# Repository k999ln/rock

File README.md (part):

# avokado / mii

miiは、声でEveに頼み、部屋に映った成果を手で操作するために開発している空間コンピューターです。

空間SIの現行研究: [mii・部屋全体を裸眼／工事なしで表示する新規開発設計](docs/mii/design/28-room-scale-si-rd.md)。共通OSを維持し、出射面の反例計算、研究部品、段階予算を整理。卓上は製品目標にせず、全室の物理成立は未実証。

**[NoahでAgentを試す](https://avoado.si/noah)**　·　[18秒で操作を見る](#catalog)

公開サイト `avoado.si` はNoahのストア・検索・実行・保存・Agent制作を入口に、必要なEve・接続・設定へ進む構成です。別企画・課金テストの画面は公開終了し、旧URLは対応する現行画面へ転送します。審査画面は審査担当だけが開けます。対象は[task139](codex/tasks/139-main-public-pages.md)、公開URLの正本は[ページ定義](services/sky-web/main-page-policy.mjs)です。

<a href="https://avocadomini.si/#technology">
  <picture>
    <source media="(prefers-reduced-motion: reduce)" srcset="docs/assets/readme/mii-tower-on-dock.webp">
    
  </picture>
</a>

*miiの外観と内部構造を描いたコンセプト映像。* [公式サイトで構造を見る](https://avocadomini.si/#technology)

[暮らしの短編](#films) · [miiの構造](#mii) · [Eveに頼む](#eve) · [Noahで探す](#catalog) · [Macで試す](#noah-mac) · [全体構成](#architecture) · [開発状況](#status) · [コードと検証](#development)

## 暮らしの中のmii

料理で両手がふさがっているとき、手を止めずに残り時間を確かめる。公式サイトの短編「料理」は、その使い心地を描いています。

*公式サイトの5本の短編。朝の光、集中するときの日よけ、外での制作、料理中のタイマー、夜の足元の灯りを描いたコンセプト映像です。*

[朝](https://d8j0ntlcm91z4.cloudfront.net/user_3ImsN7zDg5XAxCTCNf16qVkxzVQ/hf_20261028_201649_fe60d9fe-0cb2-4101-b833-4afbc7cfe769.mp4)　·　[集中](https://d8j0ntlcm91z4.cloudfront.net/user_3ImsN7zDg5XAxCTCNf16qVkxzVQ/hf_20261028_201649_1efcbbf2-15f6-4650-8089-16a7679b7ce3.mp4)　·　[創作](https://d8j0ntlcm91z4.cloudfront.net/user_3ImsN7zDg5XAxCTCNf16qVkxzVQ/hf_20261028_202029_48890df7-1fdf-49bf-b749-eae800aacdd5.mp4)　·　[料理](https://d8j0ntlcm91z4.cloudfront.net/user_3ImsN7zDg5XAxCTCNf16qVkxzVQ/hf_20261028_201647_7fafb347-3f1d-47e2-97fd-67e407a11d1c.mp4)　·　[夜](https://d8j0ntlcm91z4.cloudfront.net/user_3ImsN7zDg5XAxCTCNf16qVkxzVQ/hf_20261028_201650_242a20a0-0837-4b0a-827b-c90c76088834.mp4)

## 声と手を受け取る、4本のTowerとHub

部屋の中で表示を指すと、四方向のTowerが手の位置を捉えます。別体のHub上でRockstarOSが入力をまとめ、表示層に渡す設計です。表示層は使う空間に合わせて差し替えられます。Towerが1本のときは、Eveの機能を限定して使う想定です。

*Tower上部のセンサー帯のデザイン案。* [miiの構造](docs/structure/01-mii.md) · [R5設計](docs/avocado-mini-r5/README.md) · [V2の比較研究](docs/mii/design/v2-study/README.md)

<details>
<summary>空間入力とMaterial Inventionの実装を見る</summary>

空間入力の実装と機種設定から、手の入力がどこで処理されるかを追えます。Material Inventionには再計算用sandboxと設計資料があり、シミュレーション・実験室接続は未実装です。[空間入力のコード](lib/mii-spatial-input.ts) · [機種設定](systems/rock-star-os/targets/avocado-mini/) · [Material Inventionの設計](docs/rockstaros-avocado-mini-complete-design.md) · [製品サイトのコード](sites/avocado-mini/)

</details>

## Eveに、やりたいことを伝える

「今週の学習メモを、次に調べたいことと一緒に整理したい」。Eveでは、まず依頼を自分の言葉で書きます。入力欄の下で実行先・担当・基盤モデルを確認し、その仕事をどこに任せるか選びます。

*Web版の実画面。依頼を書いたところで、実行先はまだ接続していません。* 会話は履歴から、依頼した仕事と成果は「仕事と成果」から開けます。実行には本人確認とToolへの接続・権限が必要です。[Eveを開く](https://avoado.si/os/eve)

<details>
<summary>Eveが依頼を工程に分け、成果を検収する仕組み</summary>

### 仕事の工程と検収

Eveが目的を聞き、必要な道具とAgentを組み合わせます。AMCが工程・担当・合格条件を決め、Jevが結果を独立して検収します。下のデモでAMCの実行、別プロセスでの検収、差し戻しと再計画を試せます。成果の編集・持ち出しは、その仕事の保存方式に従います。

```sh
npm run amc:cycle -- demo
```

工程の組み合わせ、見積り、会社受注の分配を計算するライブラリと、募集文面を判定するCLIがあります。外部への応募・契約・納品・送金までの接続は開発中です。[仕事の計画](docs/sky-work-loop.md) · [実行・停止・復旧](docs/amc-goal-orchestrator.md#goalから逆算するローカル実行と再計画)

</details>

<details>
<summary>Eveのコードと担当設定</summary>

| コード | 内容 |
| --- | --- |
| [app/os/eve/](app/os/eve/) / [components/sky-chat-workspace.tsx](components/sky-chat-workspace.tsx) | 会話・仕事・Toolの画面 |
| [lib/workflow.ts](lib/workflow.ts) / [lib/work-store.ts](lib/work-store.ts) | 状態遷移・本人別保存・revision競合判定 |
| [docs/structure/04-eve-noa-amc-sky.md](docs/structure/04-eve-noa-amc-sky.md) | Eveと担当構成・実行・評価の責任 |
| mii本体の組立設計（OS共通・4 Tower＋専用Hub） | [本体HW1: 型番・端子・配線](docs/mii/design/19-body-hardware.md) / [共通OS](docs/mii/design/14-common-os.md) / [開発用検証装置](docs/mii/design/18-parts-wiring.md) |

担当設定は[全社役割台帳](data/company-role-map.json)、[営業担当台帳](data/revenue-role-map.json)、[担当別の設定](.cursor/agents/)にあります。

</details>

## Noahで、仕事に合うAgentを探す

eSIM案内と「登録情報」では、保存した氏名・メールなどを次のAgent登録にも使う目的と、送信先・項目の確認、再利用の停止を説明します。共通プロフィールは暗号化して保存します。Apple／Googleからの自動取込みと事業者への実申込は準備中です。[登録情報の再利用設計](docs/structure/03-esim.md#登録情報を次のagentでも使う2026-11-26)

本人用の[収益業務パック](docs/services/noah-revenue-pack.md)は、携帯とPCで共通のNoah画面から商品設計・納品サンプル・提案書の3担当を実行します。本人用クラウドに成果を保存し、Macの起動は不要です。無料枠を超えると待機・停止します。出力は確認用の下書きで、販売・応募・入金の完了を表しません。

*11月26日にスマホ幅390pxで開いた公開ホーム。* [旧Todayの画面](docs/assets/readme/noah-store-today.webp)

[登録フォームで生成した「法人のsi導入準備」の表紙を見る（4秒）](docs/assets/readme/noah-agent-motion.mp4)

[Noahのストア](https://avoado.si/noah)を開くと、「Agentを見つける」に接続できるAgentが並びます。上部で検索し、カテゴリや「すべて」「新しく見つかった」で絞り込めます。下へスクロールすると続きが表示されます。検索結果、保存したボード、自分のAgent、マーケットでもAgentごとの作品や仕事内容を表すカードから選べます。

作者は右上メニューの[Agentエンジニアリング](https://avoado.si/noah/engineering)でEveに目的を相談できます。実行先を確認して送ると、EveがNoahの無料クラウドで「どのAgentが何を受け取り、次に何を渡すか」を提案します。目的型なら本人の目的、収益型なら案件の成果地点と確認方法を示します。提案を読んでから試運転を選べます。紹介案件の組み合わせ例では、申込承認時と入金後の作者の取り分を見比べられます。同じ画面から自作・外部接続・動作確認・掲載申請へ進めます。

Agent登録と掲載申請では、自分の画像・動画を表紙に指定できます。迷ったときは「おまかせ生成」で、名前と説明から4秒の動画を作り、プレビューを見て選べます。CallMCPの詳細では、予約確認の依頼例と通話メモ、KaiCallsの利用条件を読んでから接続できます。購入・作者の掲載管理はストアから開けます。「法人のsi導入準備」の詳細では、業務の整理票ができるまでを15秒の短編で見られます。

専用eSIMの案内画面では利用条件と準備状況を確認できます。外部Agentに依頼するときは、提供元と送信先を確認します。[保存した成果](https://avoado.si/noah/my?view=saved&tab=results)・[eSIMの導入](https://avoado.si/connect)

保存した成果を開くと、仕事ごとの利用明細で使用量と料金の確定状況を確認できます。専用クラウドの利用権がある場合に、同じ成果一覧から仕事ごとのCPU使用量・計算料・Agent料・予約額を表示する機能も実装しています。本番での実請求は受入前です。

**[Eve・Noah 図解設計書](docs/noah/illustrated-specifications.md)**　利用者の操作、画面とバックエンド、eSIM、作者収益・作業料・定期便までを8枚の図で読めます。[共有用PDF](docs/assets/noah-illustrated-specifications.pdf)

受付中の仕事は、一覧の該当するAgentカードから開けます。「お店・会社のサイト運営」では保守・制作会社との打ち合わせに使う診断結果と確認事項を、「自分のメモ整理」では誰が何を担当するか、あとから見返せるメモを受け取れます。その時に受付可能な仕事を選べます。選ぶ前に受け取れる成果が分かり、詳細で入力・送信先を確かめて本人が依頼します。完了後は「保存した成果を見る」から開き直せます。画面とバックエンドの接続、データの取得元、初めて使う人に試してもらう手順は[初回利用の構造図](docs/noah/first-use-architecture.md)にまとめています。

基盤の仕様は[専用eSIMの発行・端末への導入・利用時の回線照合](docs/structure/03-esim.md)、[Noahクラウドの受付・実行・成果保存](docs/services/noah-cloud-agents.md)、[自社設備を含むクラウドの配置と運用](docs/compute-placement.md)にあります。公開NoahはWi-Fiや今のSIMで使えます。専用eSIMを必要とするRockstarOSの入口は模擬回線まで検証しています。Eveで担当を作る作者、Noahで依頼する利用者、外部から実入金を照合する運営のつながりは[報酬と定期便の構造図・計算例](docs/noah/eve-distribution-and-rewards.md)で確認できます。

公開Gradio APIと公開MCPに対応するAgentは、詳細の「使う」から入力して実行でき、進捗と成果をNoahの同じ仕事画面に保存します。実行中は仕事詳細を開いたままにし、保存された成果は後から再表示できます。結果通信が途切れた場合は自動再実行しません。APIのないコード紹介や提供元のGPU制限は、準備・失敗理由を表示します。

掲載リポジトリやパッケージは「使う」で提供元の公開接続定義を確認します。GitHub・npm・Dockerの公式配布記録を照合し、接続できるものはNoah内で入力・実行・成果保存へ進みます。本人認証や未対応のCLIが必要な場合は理由を表示します。掲載・定義取得・実行成功は区別します。

掲載Agentをどこまで使えるかは[実行経路別の判定表](docs/services/noah-cloud-agents.md#掲載agentの実行判定)で確認できます。11月25日に再調査した「実行準備が必要」の2,428件では、手元で8件、提供元で2件の成果を受け取りました。この対象からNoah本番で新たに成果を受け取った件数は0件です。

CLIの管理クラウドは、Memory・Filesystem・Sequential ThinkingにTime・bossの面接準備・Hermesの計画/依頼内メモを加え、公式6種類の対応機能を追加契約なしの無料枠で公開しています。対応範囲は [task125](codex/tasks/125-noah-cloud-agents.md) に記録しています。Hermes・boss-agent-cli・Time・Sequential Thinking・Memory・Filesystemの公式固定版を依頼ごとの隔離環境で動かします。標準入出力MCPの4配布物は外部通信なしのLinuxで起動・実ツール応答を確認し、Memoryの依頼間分離、Filesystemの作成/読込/作業領域外の拒否、生成物のhashも確認しました。固定応答の検査に加え、実モデル `gpt-oss-20b` で6配布物の道具実行・成果生成の成功例を手元の隔離Linuxで確認しました。空本文による継続通信の失敗を修正し、道具を実行しない完了報告は受け付けません。モデルの形式エラーによる失敗例もあり、本番クラウドでの受入とは区別します。無料のWorkers実行器は公式JavaScript本体を組み込み、3種類とも本番Noahから実モデルと公式Toolで処理し、Chrome全終了後の成果保存・再表示・ファイルの内容/hash一致を確認しました。本番の上限はUTC日ごとに本人3件・全体10件、1件240秒です（2026年11月26日確認）。Memoryの作業中の記憶は依頼ごとに分離し、出力ファイルは成果として保存します。公式TimeのMCP・bossの面接準備コマンド・Hermes本体の計画/依頼内メモは、種類ごとの非公開Python Workerで動かします。3種とも本番Noahから実モデルと公式処理を実行し、スマホ幅390pxのChromeを全終了した後のD1保存、保存一覧からの再表示・再読込・ファイルの内容/hash一致を確認しました。128MB制限での失敗はWorker分離で対処し、bossの出力上限とHermesの道具未実行も上限を増やさず補正しました。文章だけの完了を成功にはしません。Hermesのshell/一般ファイル操作、bossの求人検索/応募はこの無料版では扱いません。提供元の公開server.json、npmと公式MCP台帳、Docker公式配布記録から接続先を照合し、利用者にコード取込を求めずNoahの入力とWork保存へ進む処理も追加しています。全掲載の対応状況は `scripts/noah-agent-coverage.mjs` で点検し、定義確認を実行成功とは数えません。

11月26日に実行用Workerの配備履歴を確認し、全トラフィックを受けている版を[配備記録と受付コード](https://github.com/iceiceice999/rock/pull/58)に照合しました。Gitの `main` には、モデル使用量をUTC日ごとに本人2,400・全体8,000 neuronまでとし、件数にも本人12件・全体60件の安全上限を設ける変更があります。この変更は実行用Workerへの配備待ちです。[無料枠と配備条件](codex/tasks/125-noah-cloud-agents.md#2026-11-24-無料のクラウドを使ったモデルの量で数える)

管理クラウドの依頼は画面を閉じても実行が続き、右上メニューの「実行中」「保存した成果を見る」から本文とファイルを開けます。成果の閲覧ではAgentを再実行しません。スマホ幅390pxのChromeで全終了後の保存と再表示、実行中の停止・再読込保持を確認しています。実機Pixelの新クラウド受入とは区別します。保存済みファイルには未保存の注記を出さず、添付データが届いていない従来の結果には注記を維持します。

Agent詳細の「共有」「URLをコピー」「Xで紹介」から、個別AgentへのURLを渡せます。公開掲載中のAgentの名前・説明を共有カードへ反映し、接続情報や本人の成果は共有しません。

`https://avoado.si/` と `https://avoado.si/noah` の共有情報は、Noahのタイトル・説明・1200×630 PNGを返します。X用の大型画像カードとOpen Graphを初期HTMLに含め、画像添付なしでURL共有に使えます。

カードには元サイトの実際の評価数だけを表示します。件数のないMCP Registry等は詳細の出典で確認でき、評価として表示しません。

ホームには接続できるAgentが先に並びます。設定済みの管理クラウドで使える公式CLIも、詳細画面と同じ対応判定でこの一覧と検索へ含めます。未設定・無料版で未対応のCLIは含めません。指定した条件を保持して検索し、共通カードの一つの結果一覧に表示します。法人向け導入準備・組合せガイドの告知枠はホームから外しています。

検索は [Agentを探す](https://avoado.si/noah)、保存は [保存したもの](https://avoado.si/noah/saved) にまとめています。保存はボード・Agent・担当・成果・ファイルを切り替えます。旧URLは対応するカテゴリへ移り、Noah配下のMac専用・投稿・コミュニティー・大学別ページは撤去済みです。本人Mac Runnerの接続承認URL `/noah/mac/connect` は、接続時に発行されるコードを確認するために保持します。保存データは保持しています。

Agent詳細の最初に料金・送信先と接続ボタンを表示します。接続後は用途名で操作を選び、その行の下から依頼できます。スマホの操作一覧も、用途名・説明・確認事項を縦に並べて読めます。長い紹介は「Agentの詳細」で開けます。任せる範囲・提供者の説明は開いて確認でき、必要入力と実行を選んだ行の近くに表示します。

説明の段では、必要な準備から接続と依頼までの順番を確認できます。素材の札は、根拠を確認して公開する段階で表示します。

一覧の読み込み中はカードの形を表示し、通常の待機は花形ロゴを使います。全画面の読み込み中は、Noahのマスコット「点のトラ」がスケボーでコーンやハトをよけるゲームで遊べます（中くらいの難しさ。スペースキー・↑・タップで跳び、長く押すと高く跳ぶ）。障害物が出るたびに1/404で魔法の星が現れ、拾うと魔法使いになって8秒間無敵になります。Noahをオンラインで開き、オフライン画面の準備が済んだブラウザでは、通信が切れたときや圏外で開き直したときにも、同じトラで遊べます。接続中は透過花形ロゴの待機画面を表示し、接続成功が確定した時だけ短いポコ音と振動を返します。通常のボタン・メニュー・選択にも短いポコ音と振動を返します。音は低遅延の共通再生器を使い回し、連打を重ねず、操作のない間や非表示時には停止します。メニューの「操作の設定」で音と振動を個別に切り替え、「反応を試す」で確認できます。以前のミュート設定も保持します。動きを減らす端末設定では読み込み・押下のアニメーションを停止します。振動は対応する端末とブラウザで利用できます。 Pixel 10の公開Webで、操作音の実再生と振動の完了、Agentboardへの新規登録から認証付き実行・成果の保存・再表示まで確認済みです。受入条件と対象は[実機検証記録](codex/tasks/100-noah-standalone-ui.md#pixel-203-acceptance)と[最新mainの公開・登録から成果までの再検証](codex/tasks/125-noah-cloud-agents.md#pixel-209-and-real-model)を参照してください。

配布先は **https://avoado.si/noah**。OSの運用開始を待たずに、Noah単体で使うサービスです。閲覧・検索は登録不要です。Agentの接続などで認証が必要なときはChatGPTでサインインし、元の画面に戻ります。Noah配下ではOSランタイムを起動せず、OSやMacの導入・端末接続を利用条件にしません。共通の本人認証と成果の保存・所有者分離を再利用します。2026-11-21に独立版154を公開し、承認された10本のDB追加と一覧・依頼受付の有効化を反映しました。公開ドメインの6画面200・一覧API200・未認証の接続/依頼401を確認済みです。2026-11-22に公開版156へ更新し、応答確認済みの172件を掲載しました。本人承認の掲載担当を設定し、公開環境の390px画面で読み取り専用Agent 1件の接続→依頼→成果受領→切断後の成果保持を確認済みです。172件すべての実行成功を保証する数ではありません。`npm run noah:check:domain` で公開側を確認できます。2026-11-22の公開版163では、本人承認のAgentboardアカウント1件の外部登録→暗号化キー保存→認証付き実行→成果保持まで確認しました。本人から実スマホでAgentの実行と成果を開けたとの回答も得ています。100人分の合成試験は通過していますが、本番100人の同時利用を保証するものではありません。

以下の動画は、従来のMac向けカタログで「CowAgent」を選ぶ操作記録です。従来のカタログは公開を終了しました。Runnerの接続承認には現在も [Macを接続する](https://avoado.si/noah/mac/connect) を使います。記録動画は開発履歴として保持しています。スマホ向けの主導線はAgentの接続・依頼・成果受領で、Macを選ぶ操作は不要です。

<a href="https://avoado.si/noah/agents">
  <picture>
    <source media="(prefers-reduced-motion: reduce)" srcset="docs/assets/readme/noah-first-agent-poster.jpg">
    
  </picture>
</a>

**[NoahのAgent一覧](https://avoado.si/noah)**。スマホ向けは提供者のサーバーへ接続します。下の動画は従来のMac向け経路です。[Macの接続手順](#noah-mac)

現行の入口は [Agentを探す](https://avoado.si/noah) です。Mac向けガイドの公開ページは撤去済みです。

[CowAgentの操作動画（18秒）](https://raw.githubusercontent.com/iceiceice999/rock/main/docs/assets/readme/noah-first-agent.mp4) · [スマホで配布元を確かめるCM（20秒）](https://raw.githubusercontent.com/iceiceice999/rock/main/docs/assets/readme/noah-cm-phone-source.mp4) · [Macをつなぐ準備のCM（20秒）](https://raw.githubusercontent.com/iceiceice999/rock/main/docs/assets/readme/noah-cm-mac-runner.mp4) · [サロン用の投稿文](docs/noah/online-salon-trial.md)

<details>
<summary>Agent一覧、本人のライブラリ、セレクト・リセール</summary>

### Agent一覧と本人のライブラリ

登録済みのサービスは保存済み接続から「使う」へ進みます。画像操作で画像が届いていない仕事は「画像が未受取」と表示します。操作名は用途で表示し、元の技術名と説明は詳細へまとめます。Agent検索と絞り込みはホームの一覧で行います。登録情報と任せる範囲は人型アイコンから開き、盾・スライダー・ココナラの専用メニューは置きません。ココナラの旧入口はホームへ転送し、個別Agentは検索から開けます。`/noah/explore` は条件を保持してホームへ転送し、以前の `#timeline` からも同じ一覧を開けます。 登録情報の本文は見出しから表示し、一覧へはヘッダーのロゴで戻ります。

一覧上部は全件を標準にした一行の下線タブで、並び順と提供元は「＋」から選びます。動画付きカードは名前と短い説明を映像上に重ね、背後の明暗で文字色が反転します。本人提供予定の動画は受領後に割り当てます。

ホームでは、作者の表紙・動画・図解を使ったカードからAgentを選び、「保存」で自分のボードにまとめられます。おすすめ順には保存・フォロー・実行実績を使います。掲載元のスターや「いいね」は出典と一緒に表示します。[ピンとボードの設計](docs/noah/spec-115-pin-grid.md) · [一覧・検索・推薦の仕様](codex/tasks/140-noah-home-search.md)

「実行中」では確認待ちの仕事から開けます。仕事の詳細は受付・実行・受取の実際の状態を表示し、成果はアカウント情報・一覧カード・文章・画像に分けて表示し、元のJSONは詳細へ折りたたみます。対応する画像は実体を保持し、画像保存ボタンから対応端末の写真保存メニュー、または画像ファイルのダウンロードへ進めます。Webは写真アプリ内の保存完了までは確認しません。成果の詳細から保存・共有できます。旧 `/noah/launch` は選択Agentを保持して移動します。スマホの主導線はAgent選択→接続→依頼→成果です。従来のMac接続は専用経路に残しています。フロントと登録Agent導線は [PR #337](https://github.com/k999ln/rock/pull/337)、独立版の公開は [PR #358](https://github.com/k999ln/rock/pull/358)に記録しています。 登録画面は不足項目だけを入力し、送信情報・規約と保存再利用の説明に対する「同意して登録」で進みます。言語設定は日本語・英語・簡体字中国語・韓国語・スペイン語・アラビア語に対応し、端末言語の自動判定、手動切替、アラビア語の右から左の表示を備えます。利用者の入力や提供者の原文は翻訳しません。 最新の主要12画面と多言語UIは [PR #376](https://github.com/k999ln/rock/pull/376)に記録しています。 投稿やフォローにはサインインが必要です。[Agent一覧](https://avoado.si/noah)

*Noahの発見と接続を表すコンセプト。* 公開カタログは公開資料を使います。個人が登録したAgentは固定版を保存し、別の権限を持つ担当が審査してから公開版に追加します。公開審査には担当の設定、決済にはサービス接続と個別の確認が必要です。

Agent詳細では、接続と保存を間隔を空けて表示します。接続は紫の主ボタン、ボードへの保存は白地の補助ボタンです。

AgentごとにNoahで実行完了を確認した利用人数、1アカウント1票の王冠、公開コメントと返信を表示します。口コミはAgent詳細から確認できます。閲覧は登録不要、保存はブラウザ専用の権限で分離します。コメントには公開名を使います。外部単独利用や未同期の実行は人数に含めません。[評価とフィードバック](docs/services/noah-agent-feedback.md)。

開発者向けの `/noah/developers` では、ユーザーの声の整理・改善提案・承認後のリファクタリング・回帰試験・PR納品を運用パッケージとして案内します。相談・見積もりは **smash@avoado.si** へのメールで受け付け、ページから対象Agentを添えたメールを作成できます。Webの申込フォーム・受付履歴・運営一覧は廃止。価格・SLA・課金・作業自動実行は未設定です。[継続改善パッケージ](docs/services/noah-developer-maintenance.md)。

閲覧・検索は会員登録なし。外部Agentで登録が必要な場合は `/noah/registration` で必要項目と送信先・規約を確認し、登録Agentへ依頼できます。Agentを使う途中で必要な情報だけ追加でき、保存済みの項目は再入力せず確認・編集できます。登録シートで保存の選択・外部送信先・料金条件を確認して続けます。 Safari・Chromeに保存した情報は入力欄の自動入力候補から使えます。保存情報の取得中や読込失敗時には、同じ情報を入力し直すフォームを出しません。フォーム実行前にも入力と成果の保存、Noah中継料と提供元の未確認料金を区別して表示します。

Agentの接続にアカウントが必要な時は、`/noah/account` で「パスキーで新しく始める」と「ログイン」を最初に表示します。新規登録は最初の操作でパスキー登録を開始し、既存アカウントはパスキー・ユーザーID/パスワード・ChatGPTログインを名前で区別します。完了後は選択中のAgentと道具へ戻り、接続を続けます。入力内容はログインURLに含めません。

登録情報は `/noah/profile` から基本情報・活動プロフィール・受取口座・本人確認書類を本人専用の暗号化領域へ保存できます（受取口座と本人確認書類は、サインインした本人だけ。ブラウザだけの保存先では新しく置けず、前に置いた物の確認と削除だけできます。2026-11-23）。公開版159で提供しています。保存時に同意の版・時刻・対象を記録し、再利用の停止もできます。設定済みの登録先では、必要項目だけを選んで使い回します。Agent詳細の登録シートから元の画面を離れずに準備でき、道具ごとの「任せる／確認して実行／任せない」と全体停止をサーバーでも照合します。Agentboardの公式API登録と発行キーの暗号化保管・実行時注入を実装しています。運営が有効にした登録先だけを表示し、ブラウザ型には自作の分離ブラウザ実行基盤とスマホでの本人確認画面を実装しています。公開版163でWorkersの登録通信を修正し、Agentboardの実アカウント1件を作成して本人情報取得・成果保存まで確認しました。公開版164では確定した失敗からの再入力と以前の受付記録への復帰にも対応。応答不明の登録を再送しません。実在サービスのブラウザ登録の通し受入は未実施です。Browser Use Cloudのアカウントは不要です。実在サービスのブラウザ登録手順は未設定で、受入用の少数実行に制限しています。登録先の受付制限に対する再開時刻の表示と期限前の再送防止を追加検証中です。[登録Agentの設定・契約](docs/services/noah-registration-agent.md)。DockからのNoah起動は公開Webを直接開く[軽量アプリ](scripts/noah-web-app/README.md)に修正し、OS端末認証を通常利用の条件にしません。ブラウザ専用の保存権限は閲覧と保存済み成果の再表示に使い、Agentへ接続する時は本人アカウントを新規登録またはログインします。同じブラウザの再訪では保存先を再利用し、既存アカウントのデータを別の利用者へ移しません。外部Agent固有の登録と送信同意は、そのAgentを使う時だけ確認します。依頼受付後は同じページの進捗・成果へ進めます。登録Agentは表示中と本人確認から戻った時に同じ登録の状態だけを読み直します。外部登録の本番受入はAgentboardの公式API方式を、旧本人アカウントとPixelのブラウザ保存で個別に確認しています。実行中停止・別利用者・別Macの本番受入、任意サービスへの登録は未完了です。現在の受入範囲と残件は[Noah単体ローンチ](codex/tasks/71-noah-standalone-launch.md)を参照してください。

公開170から、ブラウザタブには背景透過の正式花形ロゴを使います。

公開173では登録済みAgentの再登録を避け、画像が届いていない依頼を未受取と表示します。用途が分かる操作名とホーム/タイムラインの切替も修正。171の収集機能を保持しています。全体verify（4,844成功・4skip）と公開ブラウザの一周を確認し、Pixelの操作接続はADBで復旧しました。本人の最新指示により、会員登録・ログインを不要にするブラウザ専用の保存権限と自動開始を実装しました。公開179で会員登録なしの利用開始と公開APIの接続→依頼→成果再表示を確認しました。Pixel 10の実機でも、Noahへの会員登録なしにTiplineの接続→検索依頼→成果5件の受取→保存から再表示まで確認しました。同じPixelのブラウザからAgentboardへ新規登録し、発行キーを入力せずに接続・本人情報取得・成果の保存と再表示まで確認しました。本番の独立ブラウザ権限100個・400要求（同時5人）の受付と所有者分離も成功。任意サービスの登録、実機ギャラリー保存、100人同時の外部実行は未受入です。eSIMは未発行で、[導入先・費用と確認事項](docs/esim/noah-pilot-rfq.md)を確認してから進めます（[PR #377](https://github.com/k999ln/rock/pull/377)）。

Agentの成果データは[保存した成果を見る](https://avoado.si/noah/saved?tab=results)から仕事を選んで開きます。旧入口の `/noah/data` と `/noah/data/saved` もこの一覧へ転送されます。Webに保存済みのNoah実行成果を本人のWorkから読み、本人が選択・同意した成果だけを運営の品質確認・不具合調査へ提供します。撤回は運営向けの写しを削除し、元の仕事を削除した後でも本人の提供履歴から取り消せます。実装は [PR #334](https://github.com/k999ln/rock/pull/334)、配備状況は [PR #358](https://github.com/k999ln/rock/pull/358)。本人が成果を取得・提供する本番通し受入は未完了です。[範囲と提供条件](docs/services/noah-result-data.md)。

### 本人用セレクト・リセール

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
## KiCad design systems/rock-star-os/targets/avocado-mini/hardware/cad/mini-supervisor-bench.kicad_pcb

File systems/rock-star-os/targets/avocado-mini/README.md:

# avocadoMini 起動・監視MCU・試験回路の開発入口

主担当はMaterial Invention／avocadoMini（ROCK）。本人の「基板はなし、そこの設計から」を受けた**Developer Previewの卓上開発**。製品名はavocadoMini、OSはRockstarOS 1.0、内部識別子は`dev.rock`。既存月額、同一契約の複数端末、AIの見積・承認・予約・usageは既存systemを使う。

## 目的と利用体験

Miniで同じ本人のEveへ入り、依頼・進捗・承認・停止・成果を扱う。監視MCUの状態はOSの観測入力へ渡す。MCUの通信やLLMの回答から本人確認、Tool成功、光学/駆動の許可を作らない。実機がない現在、実装を試せるCM5/CM5IO＋Pico 2を**卓上の参照構成**とする。これは最終Miniの部品採用・筐体寸法・電力・ゲーム性能を確定しない。

- `firmware/`: Pico 2 / RP2350 Cortex-M33用C firmware。20byte USB CDC、CRC、boot nonce/連番/設置epoch、heartbeat、ローカル再arm、停止、lease失効、watchdog。GP7はLED/低電圧ロジック専用。
- `linux/`: 実TTY driver、systemd起動設定、owner graphical sessionのEve起動、rootfs overlay生成。driverはHEARTBEAT/STOPだけを送る。ARMはdriver/APIへ公開していない。
- `hardware/cad/`: 実編集可能なKiCad回路図・2層PCB・ローカルsymbol/footprint library。USB給電のPico 2用76×62mm接点/LEDキャリア。衛星・電池・生体認識・光学を含むMini mainboardではない。
- [共通client runtime](../../../../packages/rockstaros-runtime/README.md): 既存API/本人/履歴/workflow/料金契約。native OSやvendor driverを同梱した意味ではない。
- [通信契約](../../../../contracts/avocado-mini-supervisor.json)、[試験ハーネス](hardware/cad/bench-interface.json)、[BOM候補](hardware/bench-bom.csv)。

## 責任・入出力・状態

ROCKはsource、境界、回路/PCB、hostとcross-buildの証拠。EXTERNALはCM5/Pico/BSPの供給仕様、回線契約、光学/生体部品。JOINTは組立・実起動・実GPIO/停止・熱/RF/光学の測定。OWNERは予算/採用・本人ログイン・実取引の承認。

入力はGPIO接点、CRC付きUSB状態、既存Eveのowner操作。出力は**試験LED**、期限付き観測JSON、既存Eve画面。センサーの代用接点を実温度・装着判定の受入にしない。boot nonce/USB serialは識別用で、署名済みhardware identityではない。

MCUは初期FAULT/出力OFF。5条件が正常かつheartbeatが新しい時にlocal buttonの立上りを受け、別のARM frame/leaseがある時だけLED出力可能。解除・stop・期限超過でOFF、local armを失効。dock変化でepoch更新とheartbeat/arm失効。epoch/sequence枯渇は再起動が必要。期限はsoftware設定値で、実時間の安全性測定は未完了。

## 保存・失敗・復旧・承認

- MCUはowner情報/認証token/課金を保存しない。再起動でnonceが変わる。flash書換えとproduction署名は未実施。
- driverの`health.json`は`/run/rockstaros-mini-supervisor`（0700）の一時観測。host boot monotonicの観測/失効時刻を含み、消費側は200ms期限を必ず再判定する。古いファイル・USBなし・CRC不正・再送は権限にならない。driver終了時はSTOPとファイル削除。
- Pico SDK 2.3.1のRP2350用USB VID/PIDは`2e8a:0009`（RP2040用`000a`と区別）。driverはこの値と実USB serialを照合する。SDKの開発用識別子を量産製品へ流用する許諾は未確認。実USB serialをroot所有の設定に指定するまでserviceは起動対象にならない。例の設定を実設定として使わない。serviceのenable、OS install、書込はこの生成処理では行わない。
- Eveは通常userのChromium profile（0700）で既存`https://avoado.si/os/eve`を開く。passkey/owner認証は既存browser/serverが担当。driverに資格情報を渡さない。通信・未ログイン・回線切断で既存画面の失敗を扱い、実行/請求を自動再送しない。現在の入口は**既存OS client**であり、Mini native imageの受入ではない。
- overlayは既存OSを上書きせず新しい出力directoryだけに作る。起動不能時はoverlayを取り除き、参照OSの復旧手順へ戻す。正式なA/B更新・署名boot/復旧・全損復元は未実装。

## 部品・回路の計算と制約

Pico 2の外側40pin、左右17.78mm、縦2.54mm pitchをキャリアへ展開。USBからmoduleを給電し、carrierに5V/電池入力を設けない。3V3だけを接点に出す。RP2350 A4 steppingを採用候補とし、納品chip markingを確認する。旧A2の[E9公式erratum](https://pip-assets.raspberrypi.com/categories/1214-rp2350/documents/RP-008373-DS-2-rp2350-datasheet.pdf?disposition=inline)も考慮し、外部pull-downは**4.7kΩ ±1%**（最大4.747kΩ、推奨8.2kΩ以下）にする。内部pull-downだけで断線時のLowを保証しない。[A4での改修説明](https://www.raspberrypi.com/news/rp2350-a4-rp2354-and-a-new-hacking-challenge/)も参照。

計算用上限3.6V、抵抗最小4.653kΩなら接点1本0.774mA、6本で4.643mA、抵抗損失は最大2.786mW/本。LEDは1kΩ ±1%、仮の最低VF=1.6Vで最大2.021mA。合計6.664mAは**carrier接点/LEDだけ**の仮上限で、CM5/Pico/USB/無線/光学を含む製品電力ではない。VF、許容電流、3V3 railの実仕様と温度を採用品で再確認する。6pin flag入力には部品・harnessのbounce/EMC/断線試験が必要。

J1のSTOPは**機械的に連動するDPST-NCの2接点**。1–2がSTOP_OK入力、9–10がLEDの戻り電流を直接遮断する。MCU停止時でも後者を物理的に開く。別々の無連動jumperを製品の停止ボタンとして受入しない。短い卓上wire/3V3接点専用で、laser/motor/外部電圧/安全認証を接続しない。BOMのheader/socket/LED/switch型番、land pattern、USB plugとmoduleの干渉、組立向きは未確定。

## 再現コマンド

rootから。SDK/compiler/CMakeは外部の一時領域に置き、Gitへbinary/cacheを入れない。build scriptはSDK 2.3.1のcommit/submodule、Arm GNU14.3.1、picotool commit、build中のsource不変を照合する。公式SDKの初回configureはpicotool sourceを取得する。

```sh
python3 systems/rock-star-os/targets/avocado-mini/build_firmware.py \
  --sdk /path/to/pico-sdk \
  --toolchain /path/to/arm-gnu-toolchain-14.3.rel1-darwin-arm64-arm-none-eabi \
  --cmake /path/to/cmake --output /new/build-directory
python3 -B -m unittest discover -s systems/rock-star-os/targets/avocado-mini/tests -p 'test_*.py'
cc -std=c11 -Wall -Wextra -Werror systems/rock-star-os/targets/avocado-mini/firmware/supervisor.c systems/rock-star-os/targets/avocado-mini/tests/supervisor_test.c -o /tmp/mini-supervisor-test
/tmp/mini-supervisor-test
python3 systems/rock-star-os/targets/avocado-mini/linux/stage.py --output /new/rootfs-overlay
python3 systems/rock-star-os/targets/avocado-mini/hardware/generate_bench.py --output /new/cad-directory
```

[KiCad公式CLI](https://docs.kicad.org/10.0/en/cli/cli.html)でERC、zone fill後のDRC、schematic parity、Gerber/Excellonを同一候補から生成する。検査時は別のcopyへfill/saveし、元sourceと検査済みboardのhashを両方記録する。実行した検査とsource/生成物のhashは[証拠](../../../../docs/evidence/avocado-mini-native-development.json)へ残す。警告を消すためにcheckを無効にしない。

CADの再検査/出力は `python3 systems/rock-star-os/targets/avocado-mini/hardware/check_cad.py --kicad-cli /path/to/kicad-cli --output /new/cad-export`。KiCad 10.0.7を指定し、ERC/DRC/未配線/回路図整合が全て0件の場合にGerber、Excellon、位置表、netlist、SVGとmanifestを生成する。元sourceは書き換えない。

## 合格条件・未決定の決め方

現在の成果はsource、host/PTY、cross-compiled firmware、overlay、卓上CAD。**工場の量産releaseではない**。次の順で証拠を作る。

1. exact BOM/footprint/機構を確定し、試作業者がDFM/DFAとハーネスを独立reviewする。実基板を採用し、受領chip/USB identityをbindする。
2. 同一UF2の実起動、実接点/CRC/USB抜去/MCU hang/物理stop/電源断/再起動を測定する。未受入outputはOFFを維持する。
3. CM5参照OSの同一image＋overlayでboot、owner Eve実ログイン/仕事/保存/再起動/停止を受入する。実請求を試す場合は既存見積/承認gateと別証拠。
4. native BSP、署名/更新/復旧、量産SoM/MCU・生体・深度/gesture・光学、米国でIP共有可能な衛星modem/antenna/契約、Wi-Fi AP、電池/BMS/充電/熱/RFを実機で統合する。
5. 200mm envelope・携行・裸眼表示・建築精度・ゲーム等の既存Mini gateへ合格し、最終BOM/回路/PCB/検査jig/製造指示/認証/同一閉箱測定を揃えてから工場releaseする。卓上基板の成功を移し替えない。

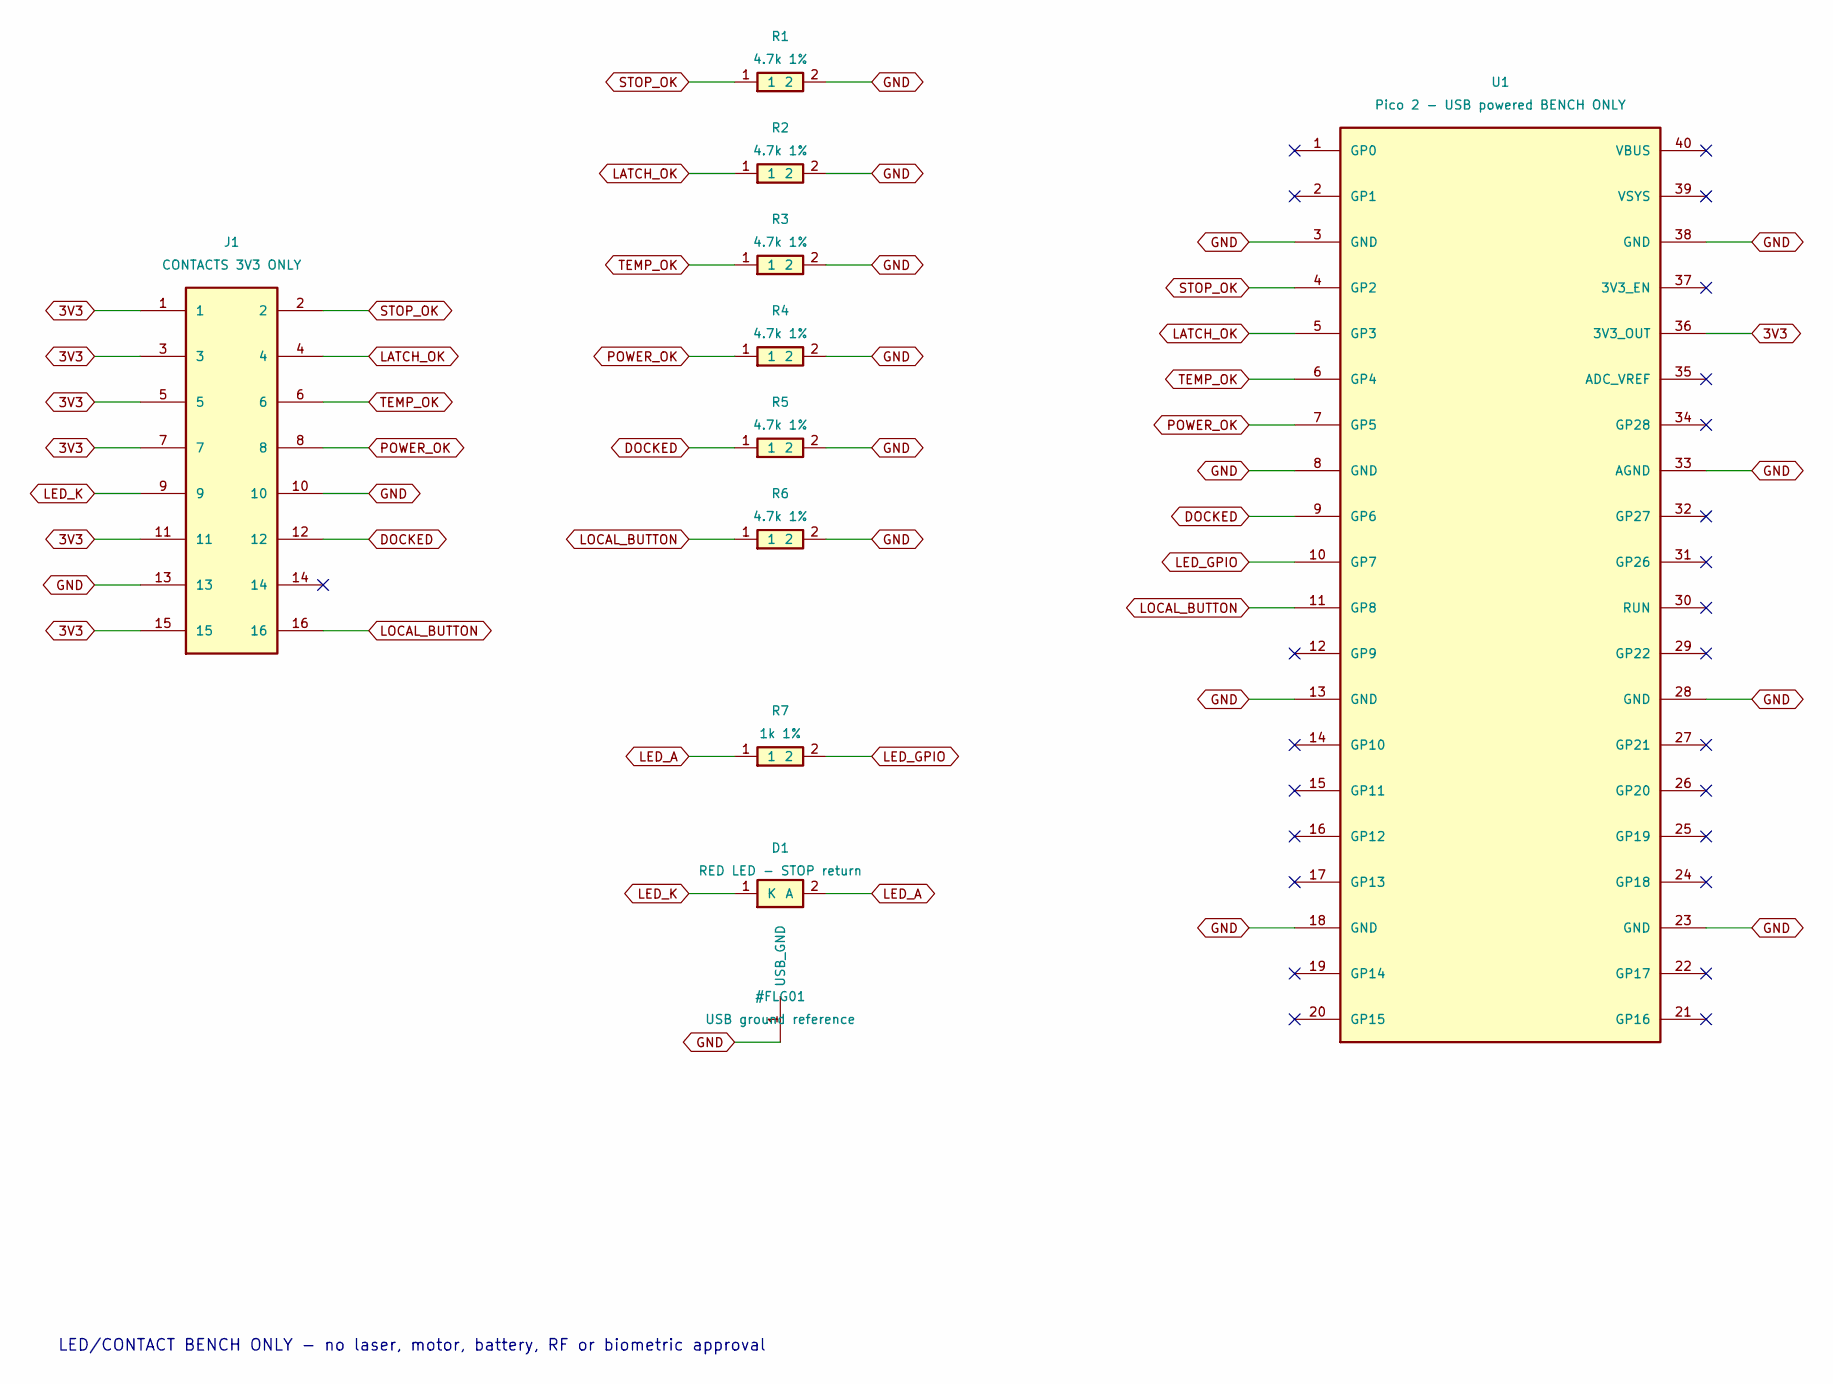
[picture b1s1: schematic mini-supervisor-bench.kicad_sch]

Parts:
D1: RED LED - STOP return; LED_0603
J1: CONTACTS 3V3 ONLY; Harness_2x08_P2.54
R1, R2, R3, R4, R5, R6: 4.7k 1%; R_0603
R7: 1k 1%; R_0603
U1: Pico 2 - USB powered BENCH ONLY; Pico2_Socket_2x20

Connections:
3V3: J1.1, J1.3, J1.5, J1.7, J1.11, J1.15, U1.36 (3V3_OUT)
DOCKED: J1.12, R5.1, U1.9 (GP6)
GND: J1.10, J1.13, R1.2, R2.2, R3.2, R4.2, R5.2, R6.2, U1.3 (GND), U1.8 (GND), U1.13 (GND), U1.18 (GND), U1.23 (GND), U1.28 (GND), U1.33 (AGND), U1.38 (GND)
LATCH_OK: J1.4, R2.1, U1.5 (GP3)
LED_A: D1.2 (A), R7.1
LED_GPIO: R7.2, U1.10 (GP7)
LED_K: D1.1 (K), J1.9
LOCAL_BUTTON: J1.16, R6.1, U1.11 (GP8)
POWER_OK: J1.8, R4.1, U1.7 (GP5)
STOP_OK: J1.2, R1.1, U1.4 (GP2)
TEMP_OK: J1.6, R3.1, U1.6 (GP4)

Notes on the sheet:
LED/CONTACT BENCH ONLY - no laser, motor, battery, RF or biometric approval

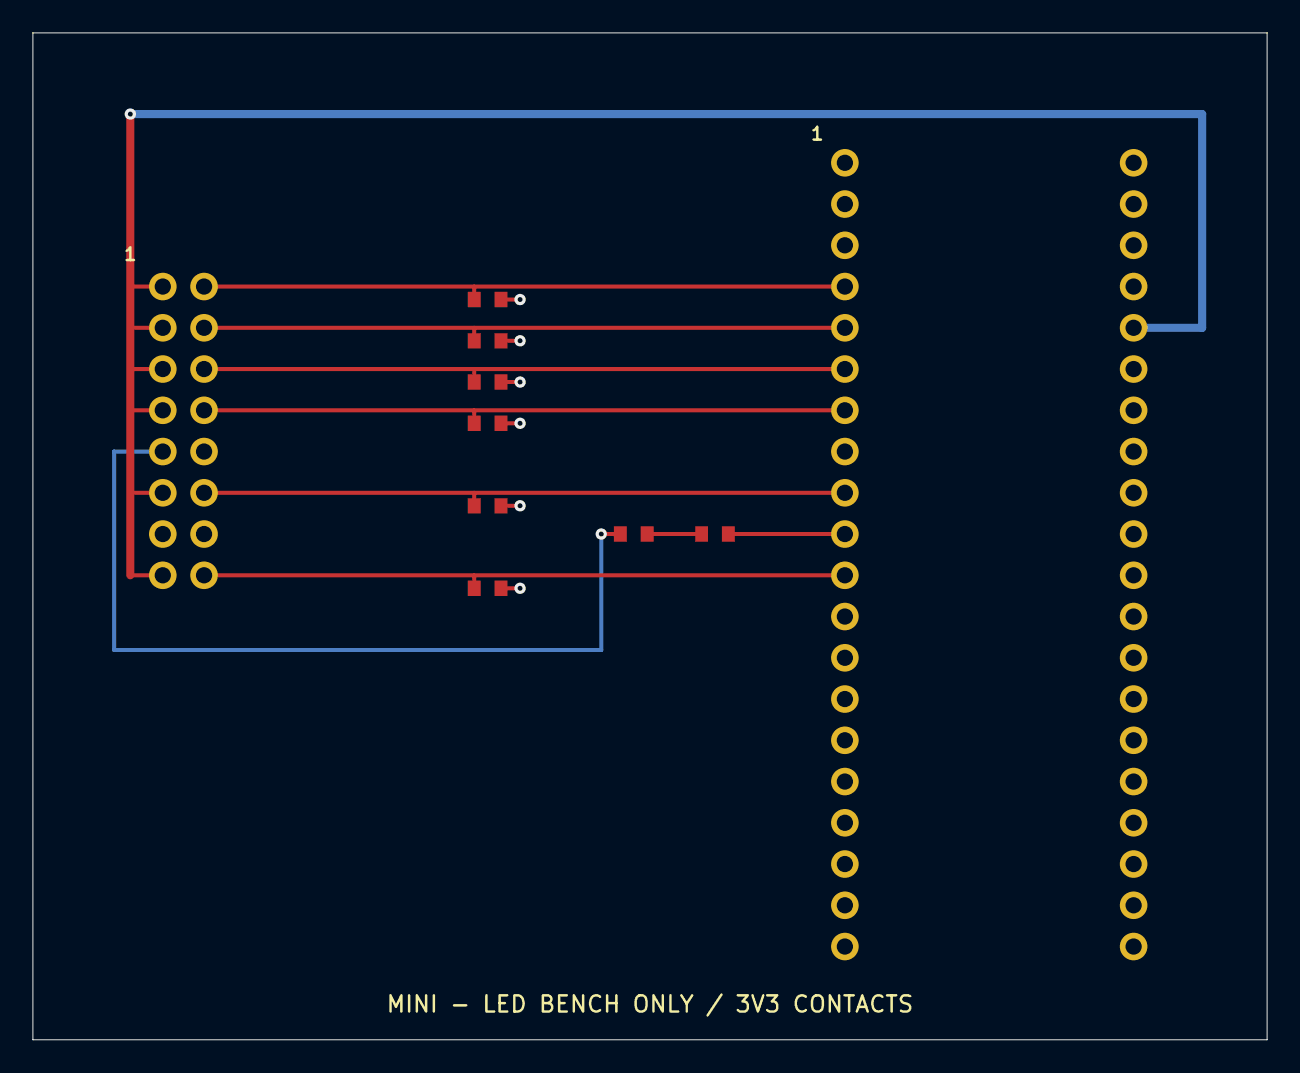
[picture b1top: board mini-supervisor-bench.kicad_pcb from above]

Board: 2 copper layers, 76.0 x 62.0 mm, 10 parts (0 on the bottom side), 11 nets.

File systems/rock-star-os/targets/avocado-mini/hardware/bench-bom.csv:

Reference,Quantity,Value,Footprint,Part selection,Release status
U1,1,Raspberry Pi Pico 2,MiniBench:Pico2_Socket_2x20,RP2350 A4 stepping preferred; verify delivered module and headers,Engineering bench only
J1,1,2x08 2.54mm header,MiniBench:Harness_2x08_P2.54,Exact keyed header and mating harness TBD,Footprint and mating review open
R1 R2 R3 R4 R5 R6,6,4.7k 1% 0603,MiniBench:R_0603,Yageo RC0603FR-074K7L candidate,Manufacturer land-pattern procurement review open
R7,1,1k 1% 0603,MiniBench:R_0603,Yageo RC0603FR-071KL candidate,Manufacturer land-pattern procurement review open
D1,1,Red LED 0603 cathode pad1,MiniBench:LED_0603,Exact LED part and forward-voltage range TBD,Polarity and land-pattern review open
STOP,1,Mechanically linked DPST NC,External J1 pairs1-2 and9-10,Exact switch and harness TBD,Independent LED-current cutoff must be measured
SOCKETS,2,1x20 2.54mm socket,Included U1 carrier pad geometry,Exact socket and USB plug clearance TBD,Mechanical review open

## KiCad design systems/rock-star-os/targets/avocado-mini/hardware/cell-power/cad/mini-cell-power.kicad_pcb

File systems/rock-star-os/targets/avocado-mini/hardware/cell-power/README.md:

# Mini 5V cell-power evaluation coupon

Purpose: develop source power switching against selected E0 image-source supply. This is a partial 5V circuit, not the Mini motherboard or qualified optical stop. Inputs: external current-limited regulated5V and 3V3 control AFTER an external NC stop. Output: switched5V for dummy load during unqualified stage. No software/firmware or settings saved. Default ON pull-down removes request on open wire; MOSFET faults and backfeeding remain unhandled.

`python3 systems/rock-star-os/targets/avocado-mini/hardware/cell-power/generate.py --output /new/cad` generates editable schematic, board with pads/nets/tracks/ground zone and libraries. `cad/` is the current generated source, not Gerber/DFM release. No ERC/DRC or real board acceptance was run. Source BOM has unresolved exact passives/connectors and land/stencil/assembly review. Do not fabricate or connect the optical source from this status.

The IC is TPS22965DSGR (not Q1): pin1/2 VIN5, pin3 ON, pin4 VBIAS5, pin5 GND, pin6 CT, pin7/8 VOUT, pad9 GND. Source: https://www.ti.com/lit/ds/symlink/tps22965.pdf . R1 1k/R2 10k gives nominal3.0V ON from3.3V. C1 10uF/C2 1uF/C3 1nF are evaluation candidates. This is not a6A board rating. At hypothetical2A and Ron25mOhm, switch loss0.10W. Thermal/inrush need actual load and layout measurements.

No current limit, reverse isolation, watchdog or independent safety cutoff is present. HDMI/USB can supply alternate current paths; switch-off has not been shown to stop light. External stop contacts, hardware faults, residual emission and actual peak need acceptance before optical connection. Owner chooses procurement and adoption; ROCK owns source; EXTERNAL supplies parts; JOINT owns measured acceptance. Existing price system unchanged.

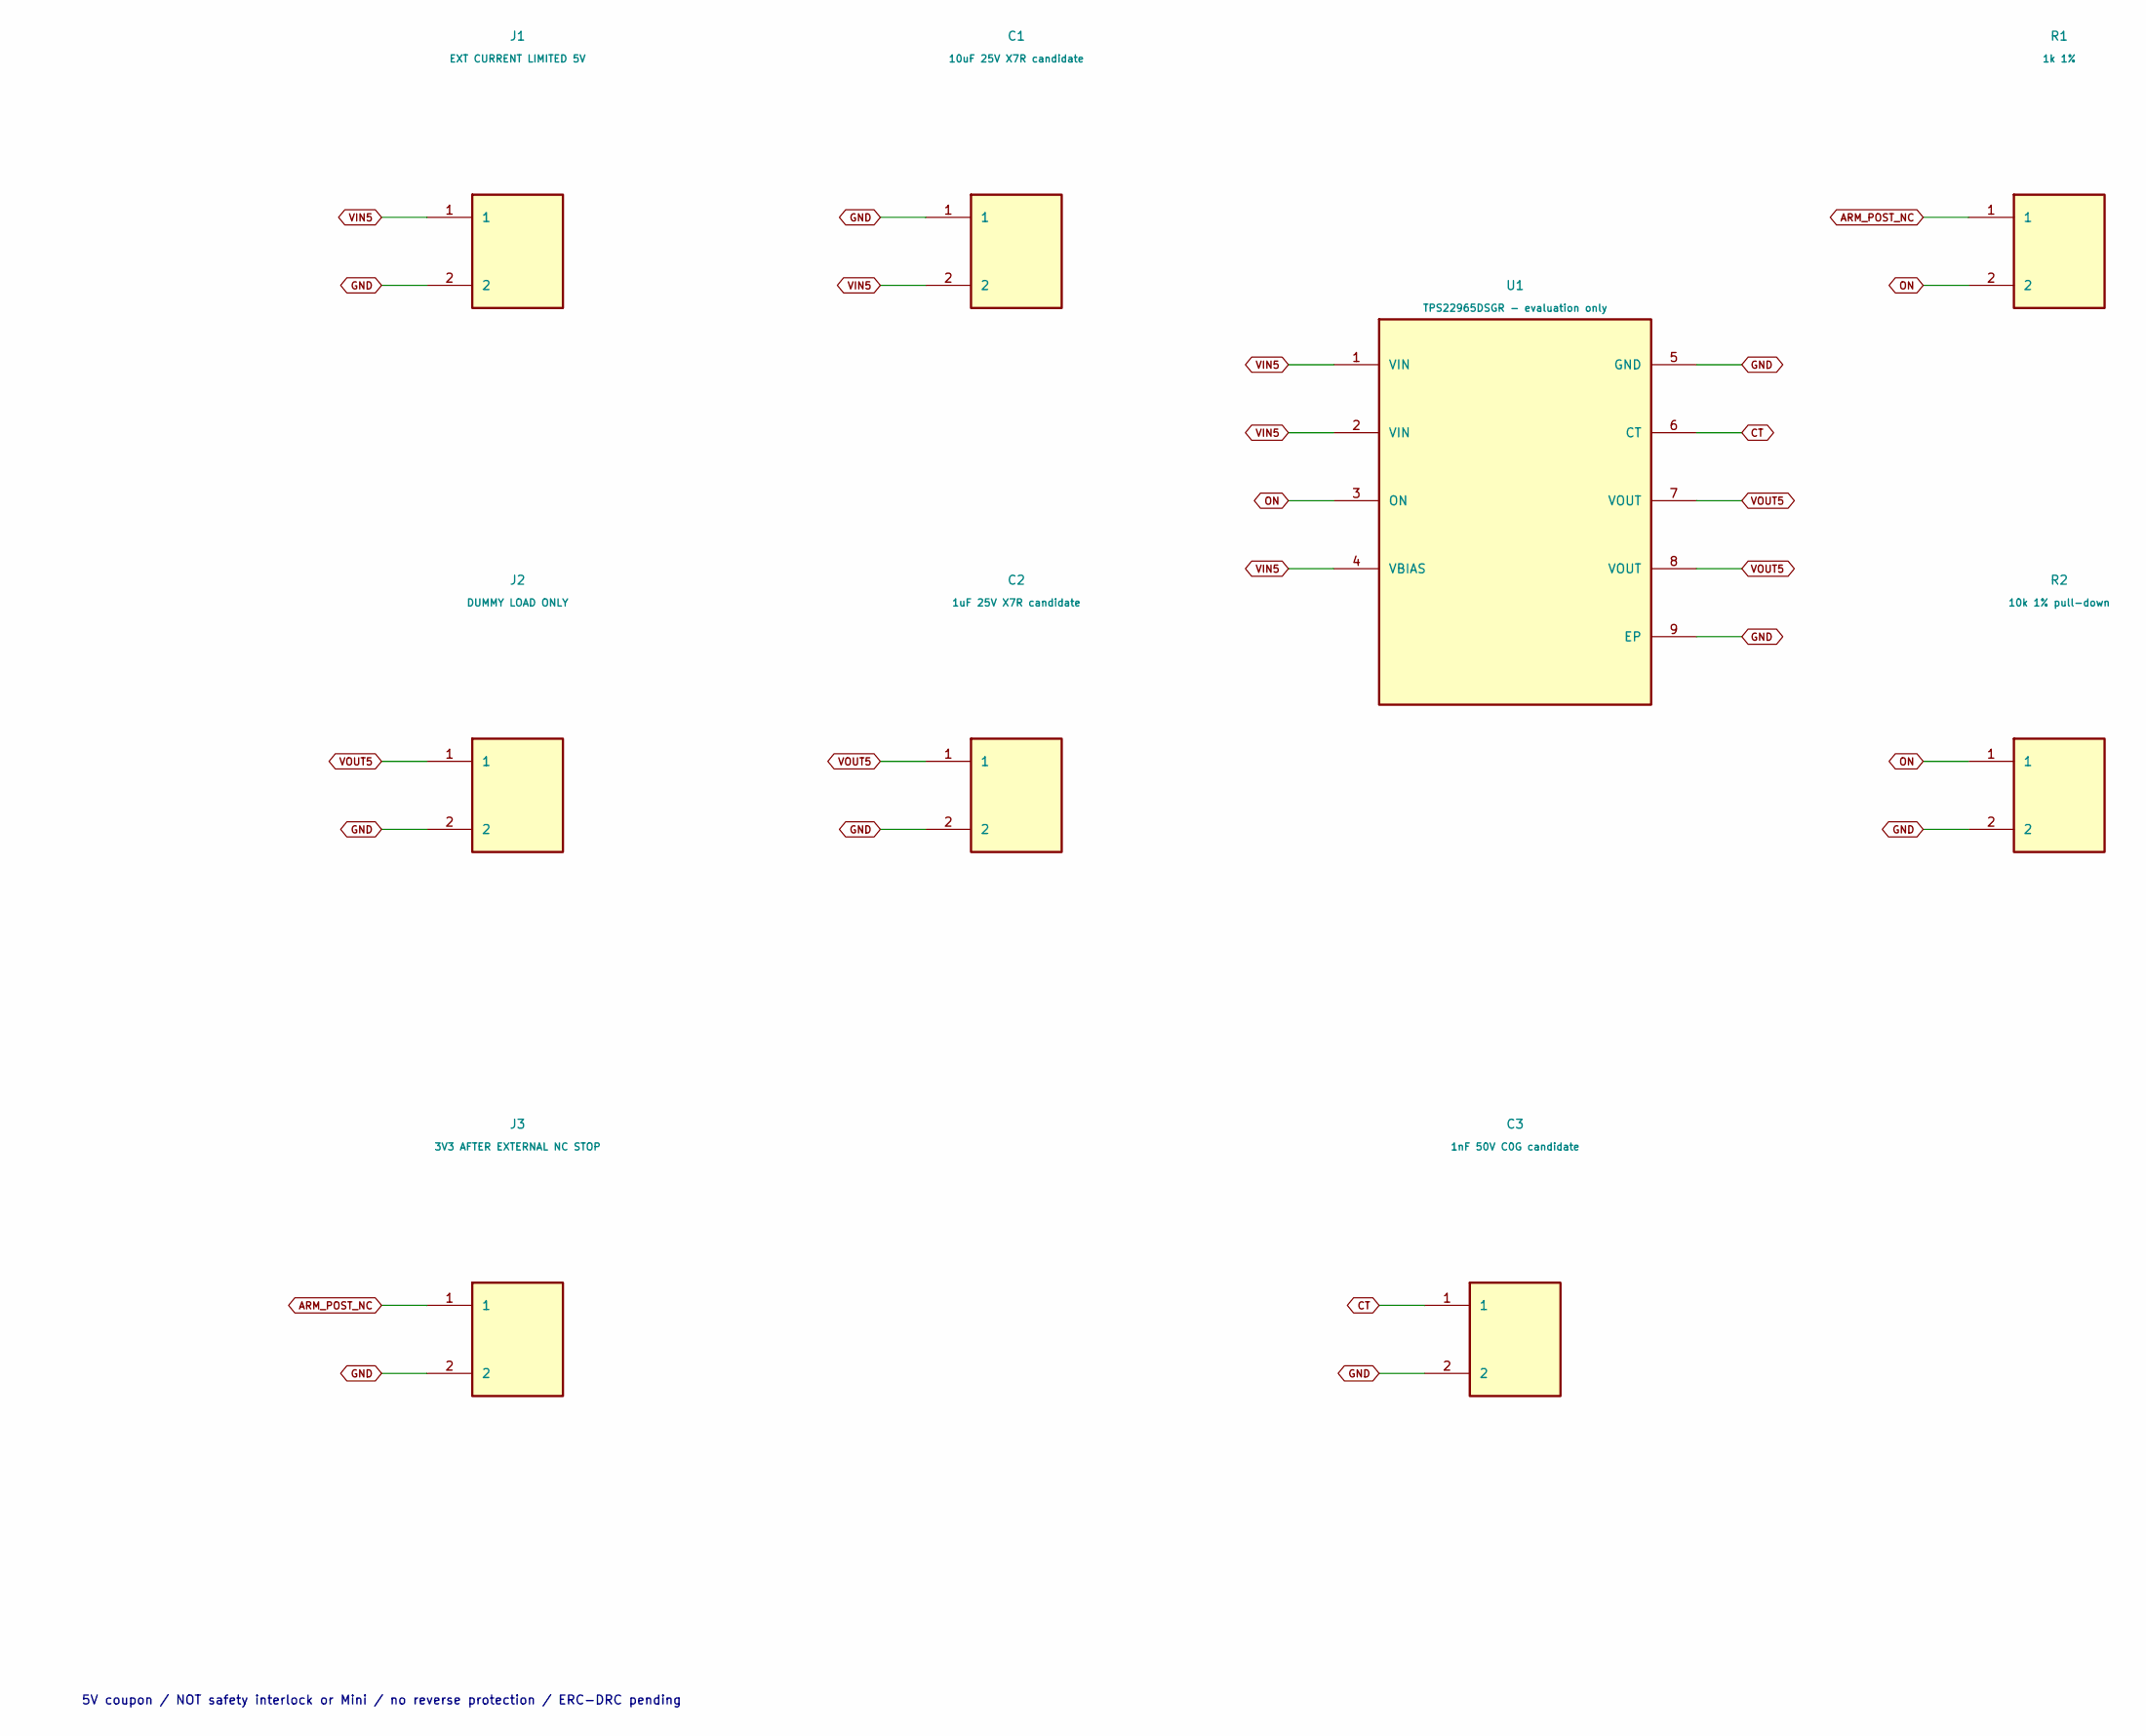
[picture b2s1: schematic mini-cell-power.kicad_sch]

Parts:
C1: 10uF 25V X7R candidate; C_0805
C2: 1uF 25V X7R candidate; C_0805
C3: 1nF 50V C0G candidate; R_C_0603
J1: EXT CURRENT LIMITED 5V; Header_1x02
J2: DUMMY LOAD ONLY; Header_1x02
J3: 3V3 AFTER EXTERNAL NC STOP; Header_1x02
R1: 1k 1%; R_C_0603
R2: 10k 1% pull-down; R_C_0603
U1: TPS22965DSGR - evaluation only; WSON8_2x2_EP

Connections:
ARM_POST_NC: J3.1, R1.1
CT: C3.1, U1.6 (CT)
GND: C1.1, C2.2, C3.2, J1.2, J2.2, J3.2, R2.2, U1.5 (GND), U1.9 (EP)
ON: R1.2, R2.1, U1.3 (ON)
VIN5: C1.2, J1.1, U1.1 (VIN), U1.2 (VIN), U1.4 (VBIAS)
VOUT5: C2.1, J2.1, U1.7 (VOUT), U1.8 (VOUT)

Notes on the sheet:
5V coupon / NOT safety interlock or Mini / no reverse protection / ERC-DRC pending

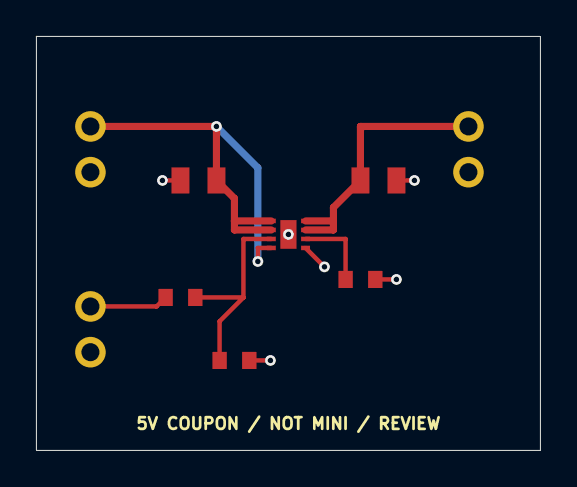
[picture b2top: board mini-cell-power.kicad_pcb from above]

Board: 2 copper layers, 28.0 x 23.0 mm, 9 parts (0 on the bottom side), 6 nets.

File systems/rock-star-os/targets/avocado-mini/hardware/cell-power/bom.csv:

Reference,Value,Part,Footprint,Status
U1,5V evaluation load switch,TPS22965DSGR,MiniCell:WSON8_2x2_EP,Selected for coupon only; TI DSG0008A land pattern review pending
C1,10uF 25V X7R,Exact manufacturer part pending,MiniCell:C_0805,Effective capacitance under DC bias not measured
C2,1uF 25V X7R,Exact manufacturer part pending,MiniCell:C_0805,Actual OLED input capacitance not included
C3,1nF 50V C0G,Exact manufacturer part pending,MiniCell:R_C_0603,Rise time requires measurement with actual load
R1,1k 1%,Exact manufacturer part pending,MiniCell:R_C_0603,3V3 signal series
R2,10k 1%,Exact manufacturer part pending,MiniCell:R_C_0603,ON default low
J1 J2 J3,1x02 2.54mm header,Exact keyed connector and mate pending,MiniCell:Header_1x02,Not touch or polarity protected
